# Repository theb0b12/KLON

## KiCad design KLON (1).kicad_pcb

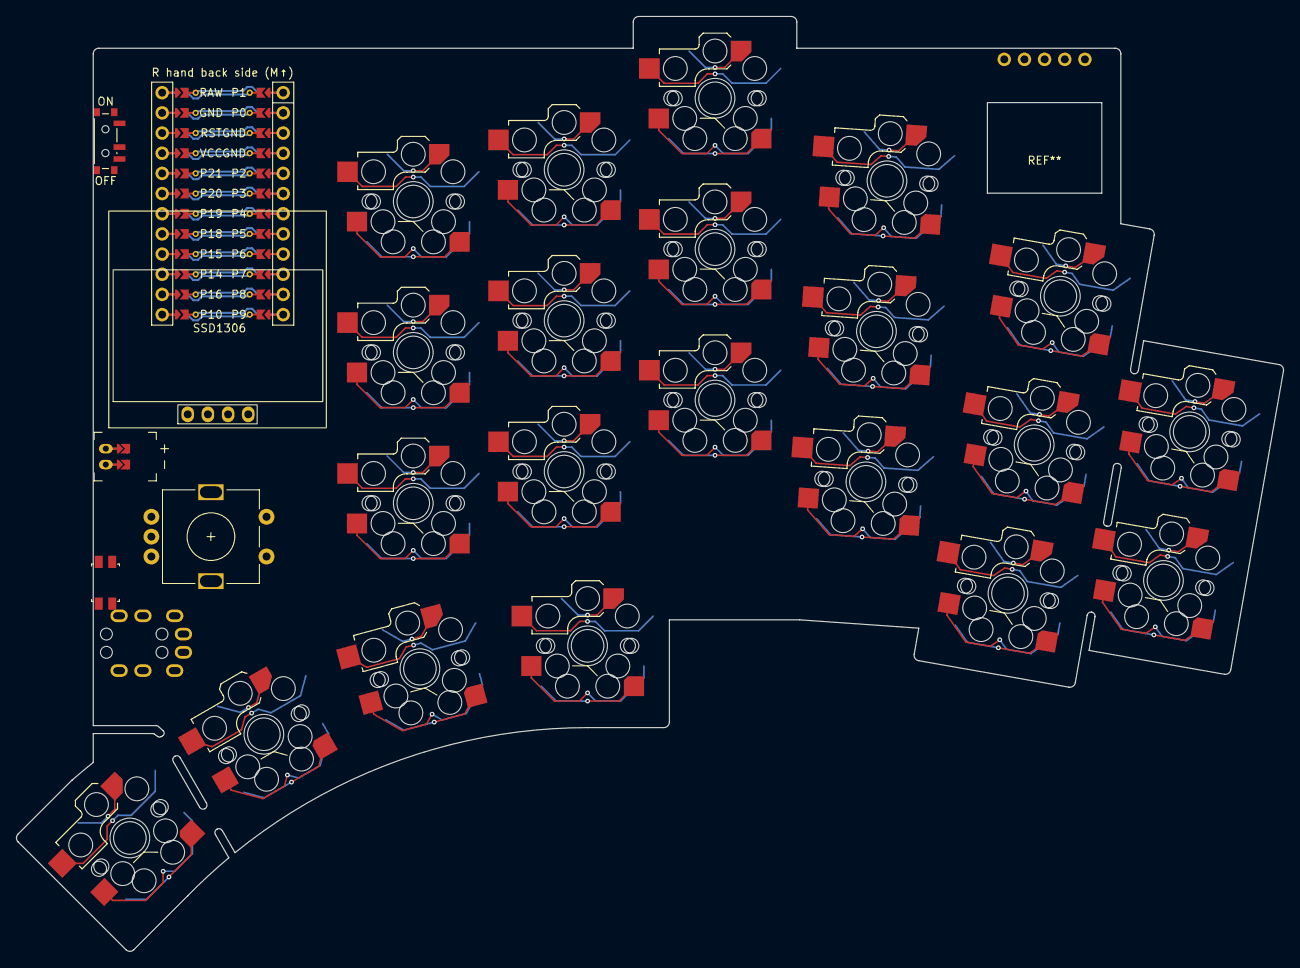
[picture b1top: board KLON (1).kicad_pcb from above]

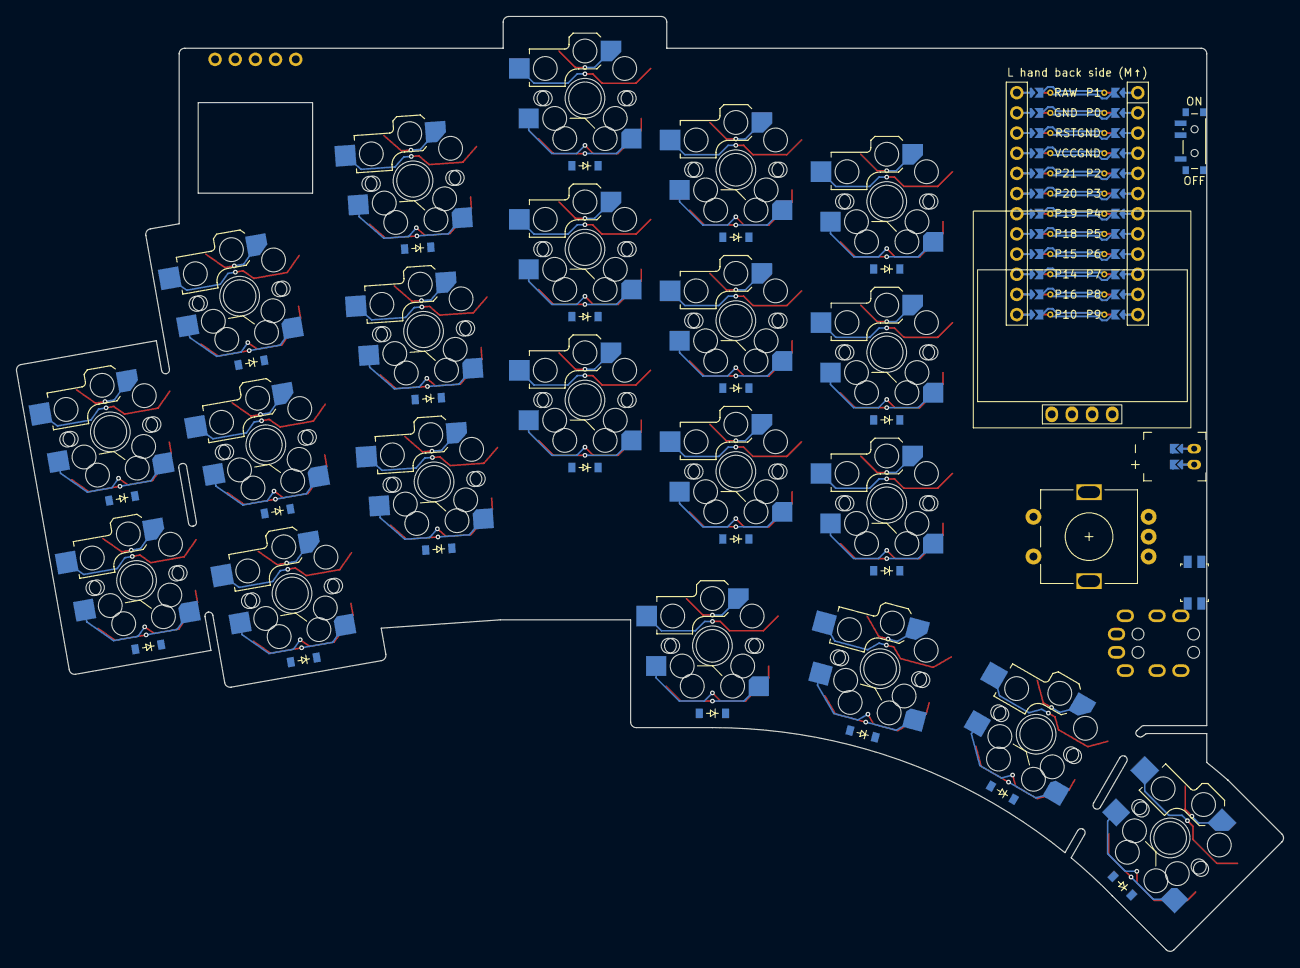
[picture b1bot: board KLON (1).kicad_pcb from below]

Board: 2 copper layers, 159.6 x 117.7 mm, 71 parts (63 on the bottom side), 28 nets.

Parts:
D1, D2, D3, D4, D5, D6, D7, D8, D9, D10, D11, D12, D13, D14, D15, D16, D17, D18, D19, D20, D21: diode_tht_sod123
JST1: battery_connector_jst_ph_2
MCU1: mcu_nice_nano
PWR1: power_switch_smd_side
RST1: reset_switch_smd_side
S1, S2, S3, S4, S5, S6, S7, S8, S9, S10, S11, S12, S13, S14, S15, S16, S17, S18, S19, S20, S21: switch_choc_v1_v2
S22, S23, S24, S25, S26, S27, S28, S29, S30, S31, S32, S33, S34, S35, S36, S37, S38, S39, S40, S41, S42: switch_mx
TRRS1: trrs_pj320a (reversible)
XX1: Pimoroni Haptic Buzz DRV2605L Driver
XX2: RotaryEncoder_Alps_EC11E-Switch_Vertical_H20mm-keebio_modif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
XX3: SSD1306_128x64OLED

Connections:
1_r0: D18.2, S18.2, S39.2
2_r0: D19.2, S19.2, S40.2
3_r0: D20.2, S20.2, S41.2
4_r0: D21.2, S21.2, S42.2
BAT_P: JST1.1, PWR1.1, PWR1.3
GND: JST1.2, MCU1.103, MCU1.104, MCU1.123, RST1.1, RST1.3
JST1_1: JST1.11, JST1.21, JST1.31
JST1_2: JST1.12, JST1.22, JST1.32
RAW: MCU1.124, PWR1.2
RST: MCU1.122, RST1.2, RST1.4
index_bottom: D4.2, S4.2, S25.2
index_home: D5.2, S5.2, S26.2
index_top: D6.2, S6.2, S27.2
inner_bottom: D1.2, S1.2, S22.2
inner_home: D2.2, S2.2, S23.2
inner_top: D3.2, S3.2, S24.2
middle_bottom: D7.2, S7.2, S28.2
middle_home: D8.2, S8.2, S29.2
middle_top: D9.2, S9.2, S30.2
pinky_bottom: D13.2, S13.2, S34.2
pinky_extra_bottom: D16.2, S16.2, S37.2
pinky_extra_home: D17.2, S17.2, S38.2
pinky_home: D14.2, S14.2, S35.2
pinky_top: D15.2, S15.2, S36.2
ring_bottom: D10.2, S10.2, S31.2
ring_home: D11.2, S11.2, S32.2
ring_top: D12.2, S12.2, S33.2
undefined: XX1.1, XX1.2, XX1.3, XX1.4, XX1.5, XX2.A, XX2.B, XX2.C, XX2.MP, XX2.S1, XX2.S2, XX3.1, XX3.2, XX3.3, XX3.4
